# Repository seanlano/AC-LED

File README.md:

# AC-LED

A KiCad schematic and PCB design for a circuit to power a Cree CXA1507 36 volt COB LED directly from a 240 volts AC supply. The 36 volt variant of the CXA1507 draws 200 mA, so this design would work with any LED unit that draws this current. 

## Warning 

**Use this design at your own risk!** Working with high voltage AC is _extremely_ dangerous, and may even be illegal in some areas if not authorised. I make absolutely no guarantee of safety or fitness for purpose of this design. 

## Licence

Copyright Sean Lanigan 2017.

This documentation describes Open Hardware and is licensed under the CERN OHL v. 1.2. You may redistribute and modify this documentation under the terms of the CERN OHL v.1.2. (http://ohwr.org/cernohl). This documentation is distributed WITHOUT ANY EXPRESS OR IMPLIED WARRANTY, INCLUDING OF MERCHANTABILITY, SATISFACTORY QUALITY AND FITNESS FOR A PARTICULAR PURPOSE. Please see the CERN OHL v.1.2 for applicable conditions.

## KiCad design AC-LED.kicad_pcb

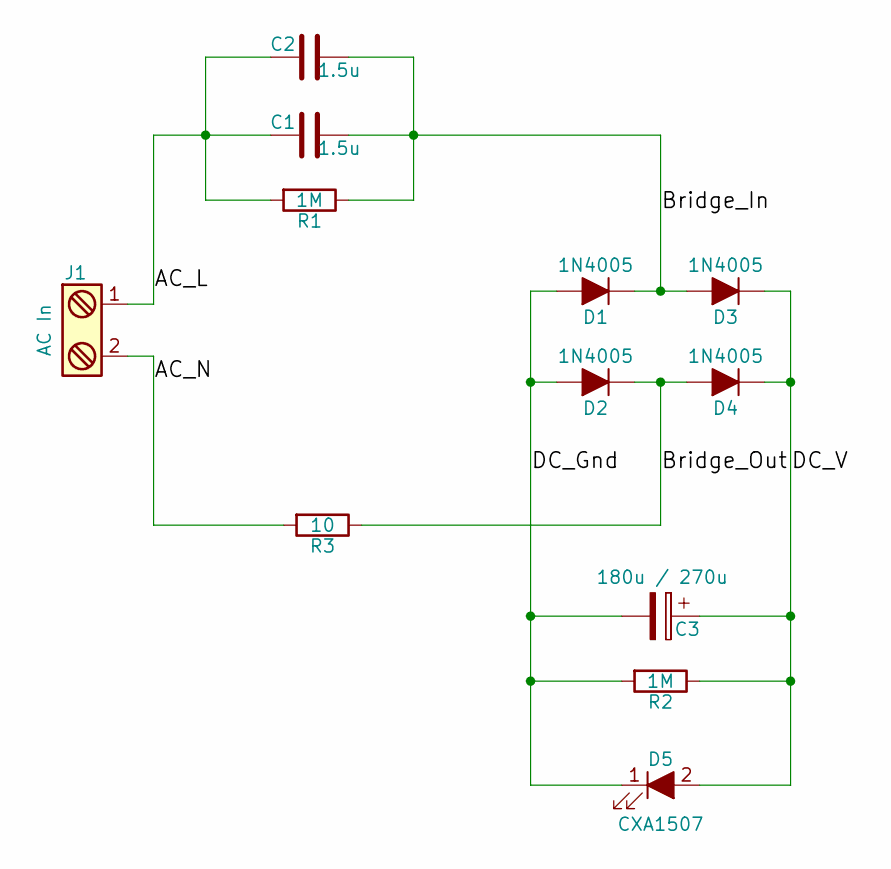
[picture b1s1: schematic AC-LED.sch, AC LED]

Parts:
C1, C2: 1.5u; Large_Cap-Multi
C3: 180u / 270u; C_Radial_D13_L21_P5
D1, D2, D3, D4: 1N4005; Diode_DO-41
D5: CXA1507; 2_wire_5mm-0.9OD
J1: AC In; Terminal
R1: 1M; Res_Long_Small
R2: 1M; Res_Short_Small
R3: 10; Res_Long_Large

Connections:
/AC_L: C1.1, C2.1, J1.1, R1.2
/AC_N: J1.2, R3.2
/Bridge_In: C1.2, C2.2, D1.1 (K), D3.2 (A), R1.1
/Bridge_Out: D2.1 (K), D4.2 (A), R3.1
/DC_Gnd: C3.2, D1.2 (A), D2.2 (A), D5.1 (K), R2.2
/DC_V: C3.1, D3.1 (K), D4.1 (K), D5.2 (A), R2.1

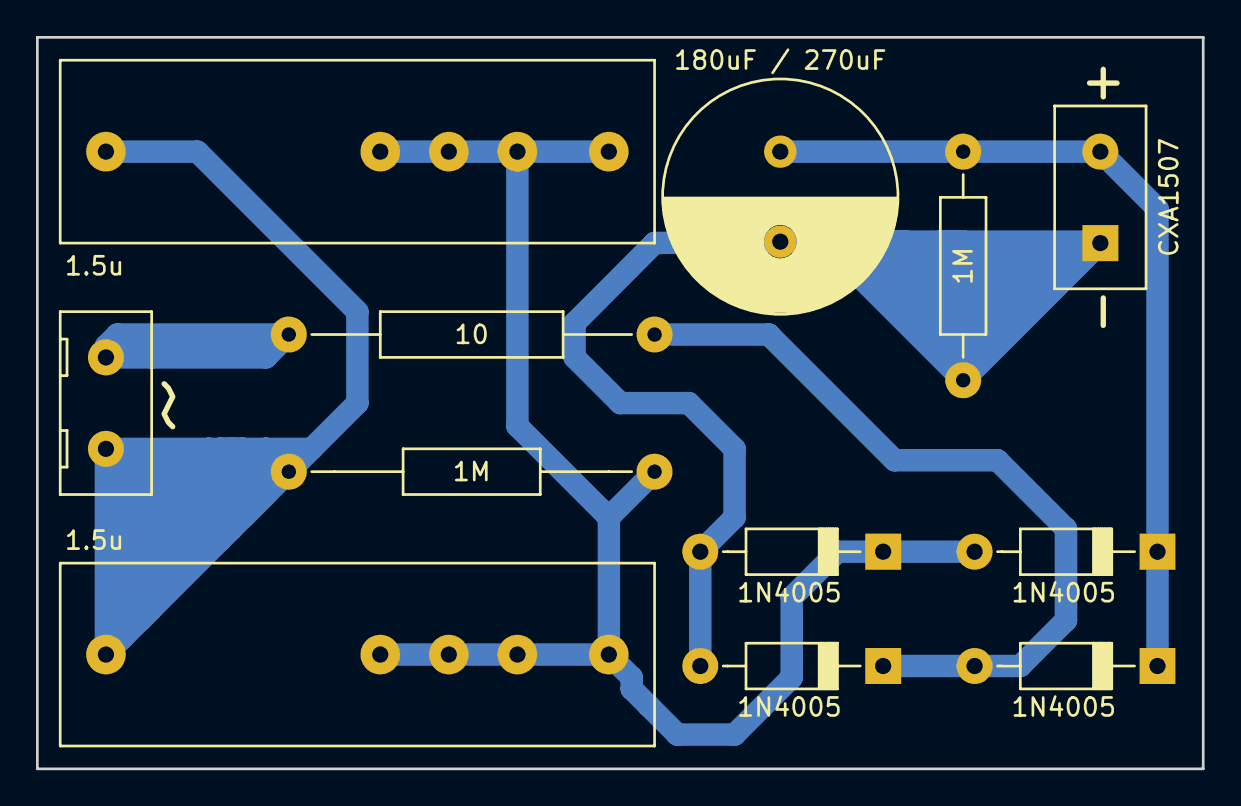
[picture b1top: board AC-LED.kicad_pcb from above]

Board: 2 copper layers, 64.8 x 40.6 mm, 12 parts (0 on the bottom side), 6 nets.

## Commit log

2017-06-18 Create initial README
2017-06-18 Initial upload

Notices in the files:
AC-LED.kicad_pcb:
Licenced under CERN OHL v1.2 or later
